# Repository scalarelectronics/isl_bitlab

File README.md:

# isl_bitlab
Electronics design &amp; CAM files for ISL littleBits

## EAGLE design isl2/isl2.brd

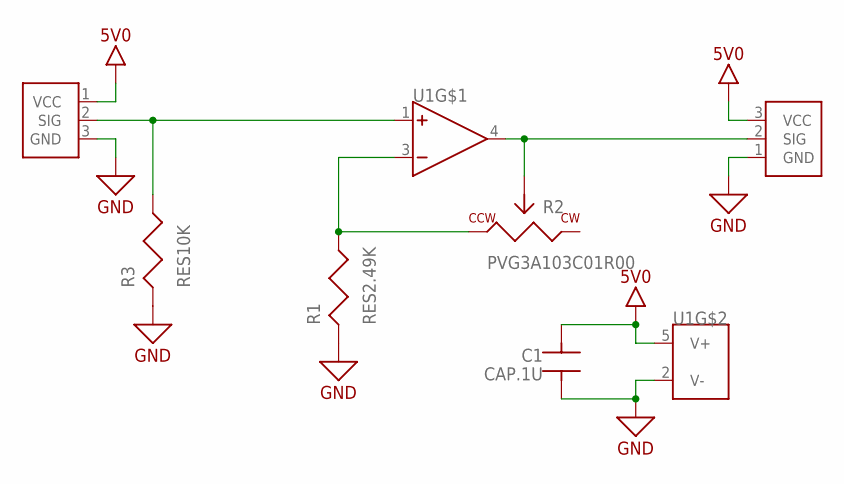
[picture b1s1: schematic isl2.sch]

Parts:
C1: CAP.1U; SMT0603
J1: BITSNAPINPUT; BITSNAP_INPUT_MALE
J2: BITSNAPOUTPUT; BITSNAP_OUTPUT_FEMALE
R1: RES2.49K; SMT0603
R2: PVG3A103C01R00; PVG3A
R3: RES10K; SMT0603
U1: LMV321; SOT23-5

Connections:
5V0: C1.2, J1.1 (VCC), J2.3 (VCC), U1.5 (V+)
GND: C1.1, J1.3 (GND), J2.1 (GND), R1.1, R3.1, U1.2 (V-)
unnamed: J1.2 (SIG), R3.2, U1.1 (IN+)
unnamed: R1.2, R2.1 (CCW), U1.3 (IN-)
unnamed: J2.2 (SIG), R2.2 (WIPER), U1.4 (OUT)

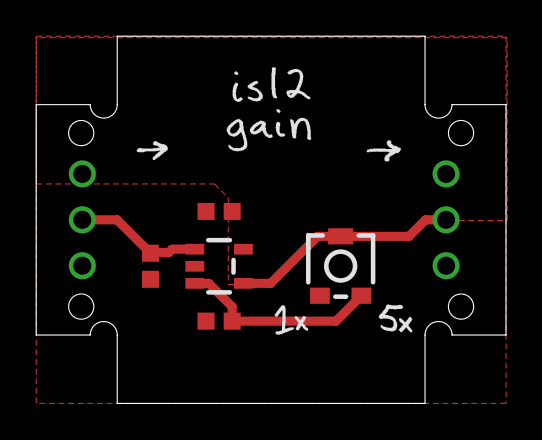
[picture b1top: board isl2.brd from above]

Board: 2 copper layers, 26.1 x 20.4 mm, 14 parts (1 on the bottom side), 5 nets.

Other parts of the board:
U$8: ISL2_LABEL
U$10: OSHW_FILLX150_NOTEXT
U$11: ISL_LOGO
U$12: 1X_LABEL
U$13: ARROW
U$14: ARROW2
U$15: 5X_LABEL

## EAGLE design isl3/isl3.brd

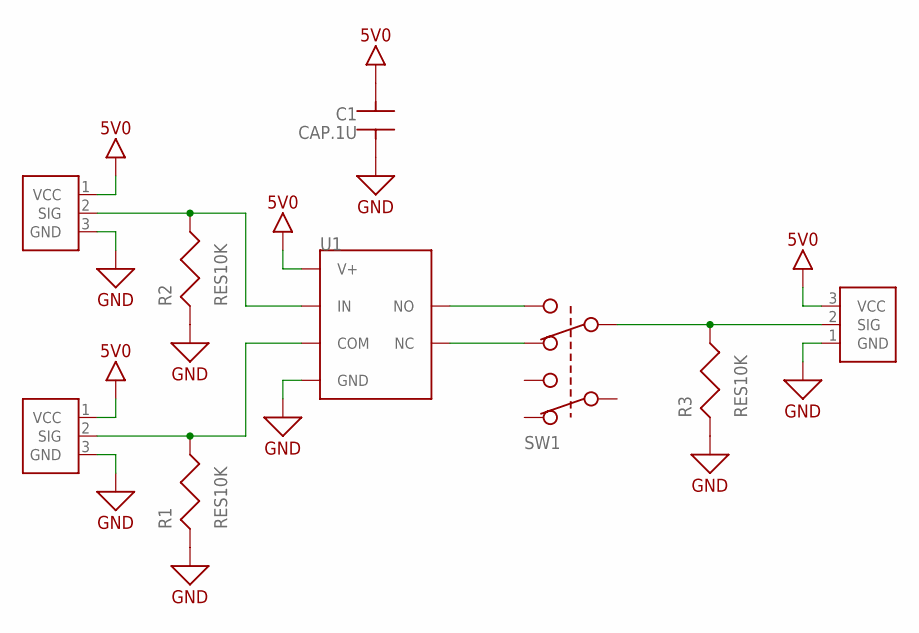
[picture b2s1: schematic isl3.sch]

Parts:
C1: CAP.1U; SMT0603
J1, J3: BITSNAPINPUT; BITSNAP_INPUT_MALE
J2: BITSNAPOUTPUT; BITSNAP_OUTPUT_FEMALE
R1, R2, R3: RES10K; SMT0603
SW1: AYZ0202AGRLC
U1: TS5A3160DBVR; SOT23-6

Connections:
5V0: C1.2, J1.1 (VCC), J2.3 (VCC), J3.1 (VCC), U1.5 (V+)
GND: C1.1, J1.3 (GND), J2.1 (GND), J3.3 (GND), R1.1, R2.1, R3.1, U1.2 (GND)
unnamed: J1.2 (SIG), R2.2, U1.6 (IN)
unnamed: J3.2 (SIG), R1.2, U1.4 (COM)
unnamed: SW1.6 (NO_B), U1.1 (NO)
unnamed: SW1.4 (NC_B), U1.3 (NC)
unnamed: J2.2 (SIG), R3.2, SW1.5 (COM_B)

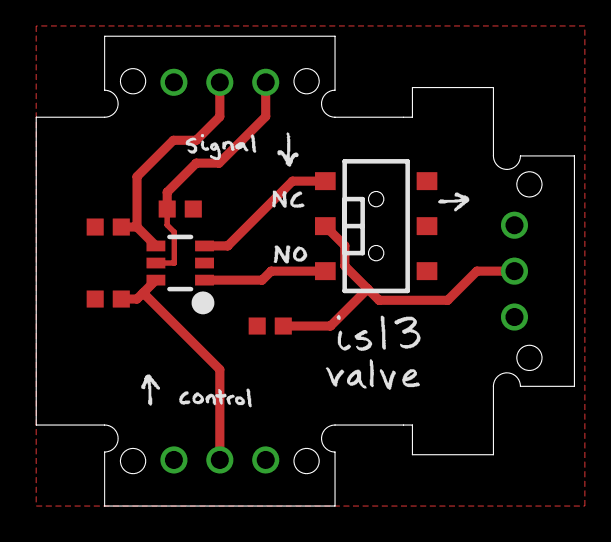
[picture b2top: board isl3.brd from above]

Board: 2 copper layers, 29.9 x 26.1 mm, 19 parts (1 on the bottom side), 7 nets.

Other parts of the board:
U$10: OSHW_FILLX150_NOTEXT
U$11: ISL_LOGO
U$12: ISL3_LABEL
U$13, U$18: ARROW
U$14: ARROW2
U$19: NC_LABEL
U$20: NO_LABEL
U$21: SIGNAL_LABEL
U$22: CONTROL_LABEL

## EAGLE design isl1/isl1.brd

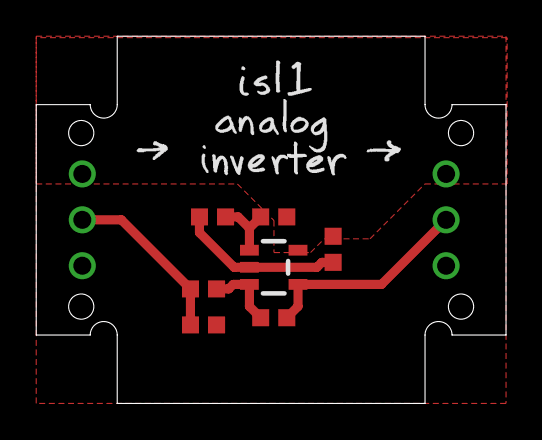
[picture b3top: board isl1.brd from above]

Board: 2 copper layers, 26.1 x 20.4 mm, 14 parts (1 on the bottom side), 6 nets.

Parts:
C1: CAP.1U; SMT0603
J1: BITSNAPINPUT; BITSNAP_INPUT_MALE
J2: BITSNAPOUTPUT; BITSNAP_OUTPUT_FEMALE
R1, R2, R3, R4, R5: RES10K; SMT0603
U1: LMV321; SOT23-5
U$10: OSHW_FILLX150_NOTEXT
U$11: ISL_LOGO
U$12: ISL1_LABEL
U$13: ARROW
U$14: ARROW2

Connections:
5V0: C1.2, J1.1, J2.3, R3.1, U1.5
GND: C1.1, J1.3, J2.1, R4.1, R5.1, U1.2
unnamed: J1.2, R2.1, R5.2
unnamed: R1.1, R2.2, U1.3
unnamed: R3.2, R4.2, U1.1
unnamed: J2.2, R1.2, U1.4

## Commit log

2016-09-29 Initial upload commit
